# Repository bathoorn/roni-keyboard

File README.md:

# roni-keyboard
kicad roni keyboard project

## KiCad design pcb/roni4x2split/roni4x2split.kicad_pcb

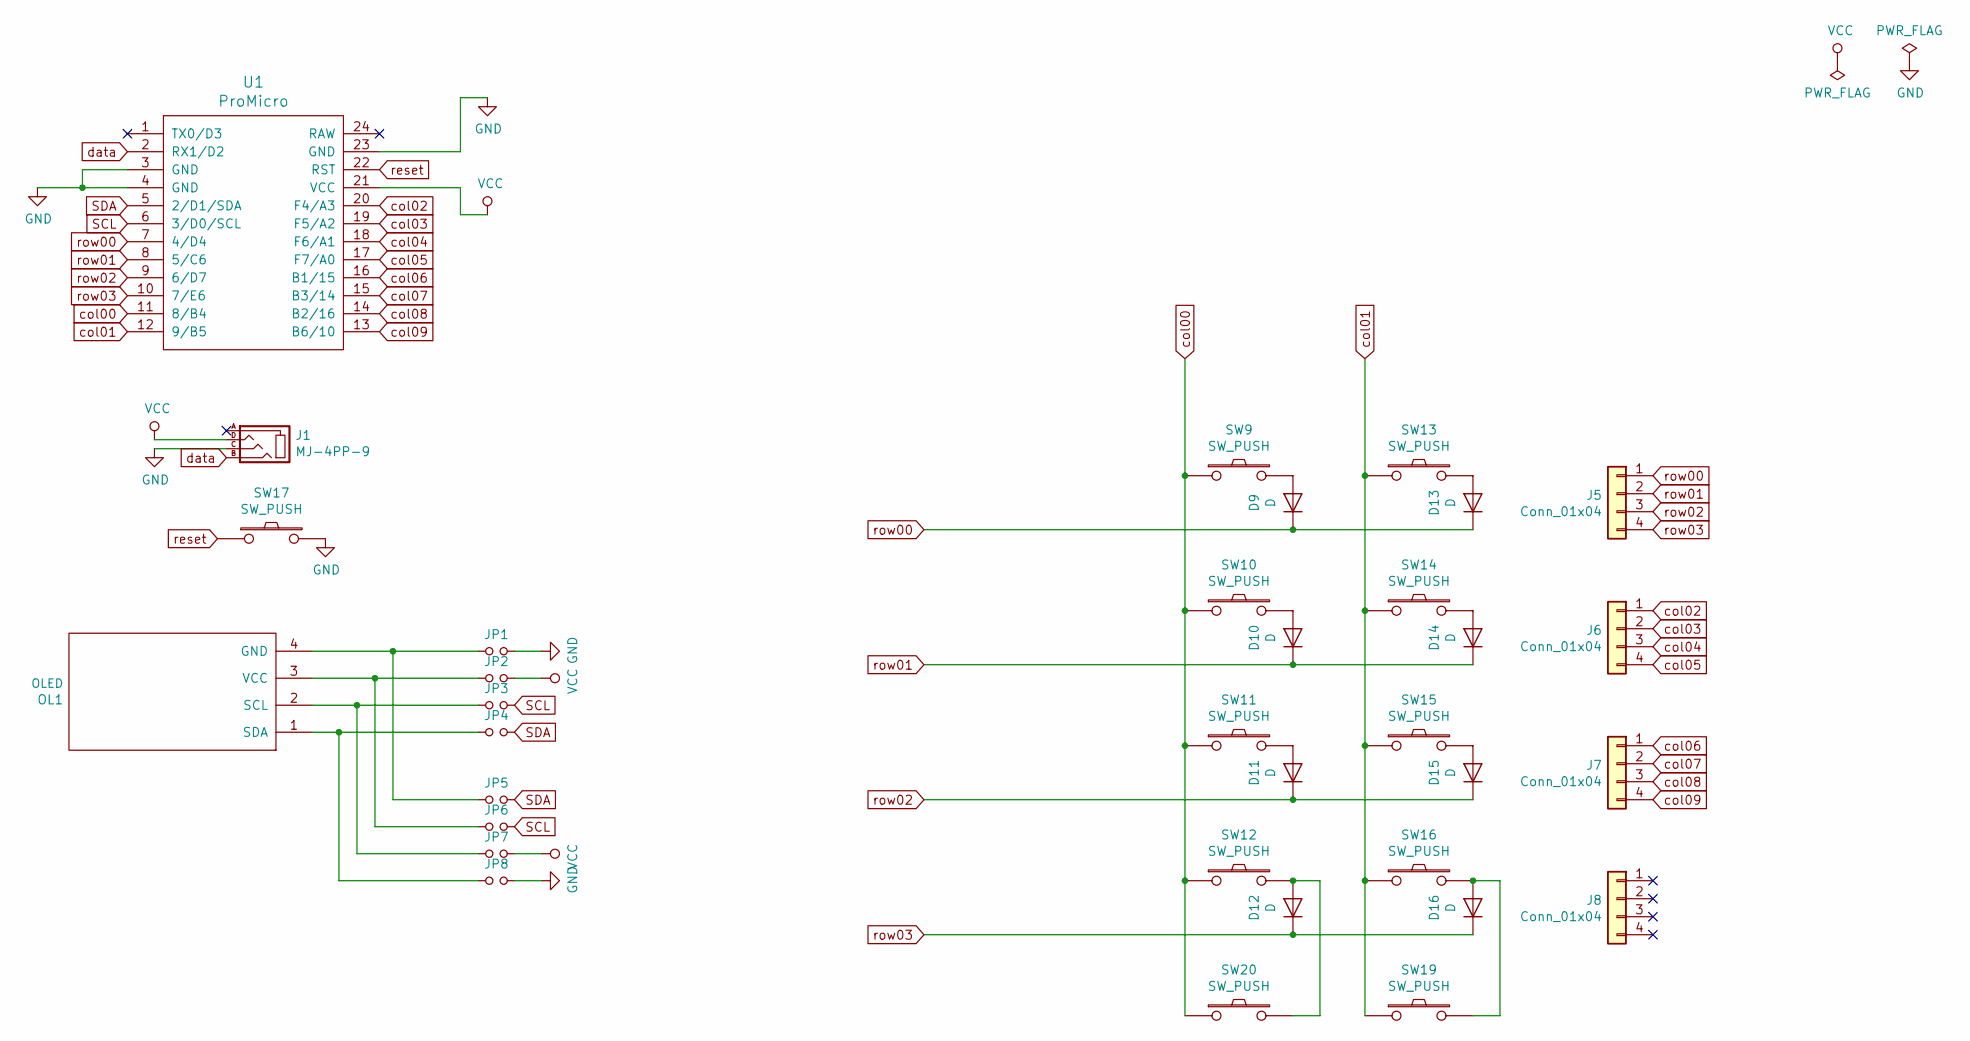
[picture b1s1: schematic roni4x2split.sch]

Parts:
D9, D10, D11, D12, D13, D14, D15, D16: D; D3_TH_SMD
J1: MJ-4PP-9
J5, J6, J7, J8: Conn_01x04; J_1x04_P2.00mm_Vertical
JP1, JP2, JP3, JP4, JP5, JP6, JP7, JP8: Jumper_NO_Small; Jumper
OL1: OLED
SW9, SW10, SW11, SW12, SW13, SW14, SW15, SW16, SW19, SW20: SW_PUSH; SW_MX_reversible
SW17: SW_PUSH; ResetSW
U1: ProMicro; ProMicro_v2

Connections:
GND: J1.C, JP1.2, JP8.2, SW17.2, U1.3 (GND), U1.4 (GND), U1.23 (GND)
unnamed: D9.2 (A), SW9.2
unnamed: D10.2 (A), SW10.2
unnamed: D11.2 (A), SW11.2
unnamed: D12.2 (A), SW12.2, SW20.2
unnamed: D13.2 (A), SW13.2
unnamed: D14.2 (A), SW14.2
unnamed: D15.2 (A), SW15.2
unnamed: D16.2 (A), SW16.2, SW19.2
unnamed: JP1.1, JP5.1, OL1.4 (GND)
unnamed: JP2.1, JP6.1, OL1.3 (VCC)
unnamed: JP3.1, JP7.1, OL1.2 (SCL)
unnamed: JP4.1, JP8.1, OL1.1 (SDA)
SCL: JP3.2, JP6.2, U1.6 (3/D0/SCL)
SDA: JP4.2, JP5.2, U1.5 (2/D1/SDA)
VCC: J1.D, JP2.2, JP7.2, U1.21 (VCC)
col00: SW9.1, SW10.1, SW11.1, SW12.1, SW20.1, U1.11 (8/B4)
col01: SW13.1, SW14.1, SW15.1, SW16.1, SW19.1, U1.12 (9/B5)
col02: J6.1, U1.20 (F4/A3)
col03: J6.2, U1.19 (F5/A2)
col04: J6.3, U1.18 (F6/A1)
col05: J6.4, U1.17 (F7/A0)
col06: J7.1, U1.16 (B1/15)
col07: J7.2, U1.15 (B3/14)
col08: J7.3, U1.14 (B2/16)
col09: J7.4, U1.13 (B6/10)
data: J1.B, U1.2 (RX1/D2)
reset: SW17.1, U1.22 (RST)
row00: D9.1 (K), D13.1 (K), J5.1, U1.7 (4/D4)
row01: D10.1 (K), D14.1 (K), J5.2, U1.8 (5/C6)
row02: D11.1 (K), D15.1 (K), J5.3, U1.9 (6/D7)
row03: D12.1 (K), D16.1 (K), J5.4, U1.10 (7/E6)

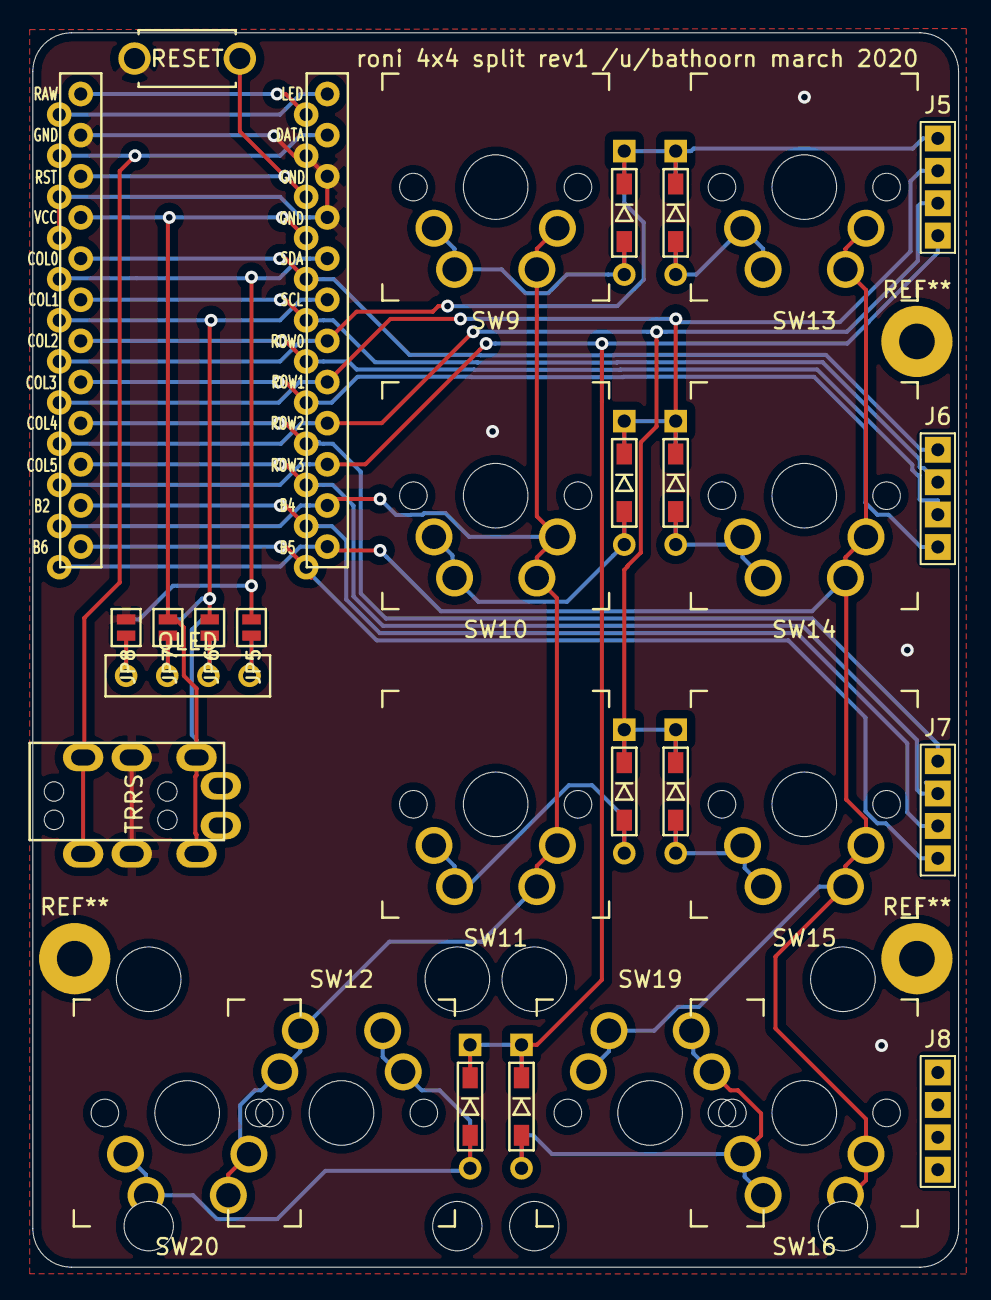
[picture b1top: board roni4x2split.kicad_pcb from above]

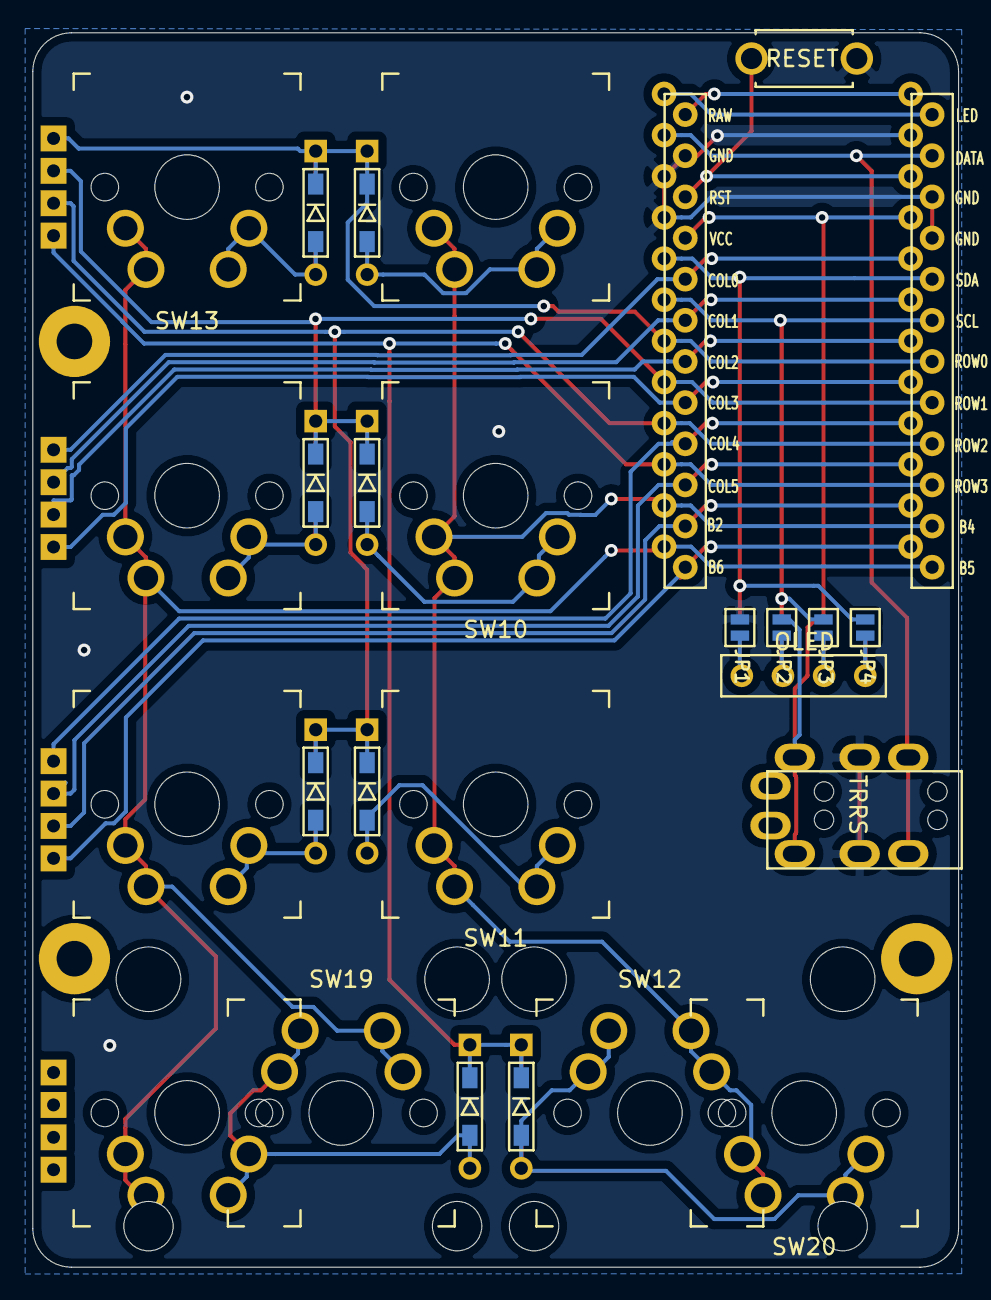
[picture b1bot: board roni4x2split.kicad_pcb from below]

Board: 2 copper layers, 57.1 x 76.2 mm, 34 parts (4 on the bottom side), 32 nets.

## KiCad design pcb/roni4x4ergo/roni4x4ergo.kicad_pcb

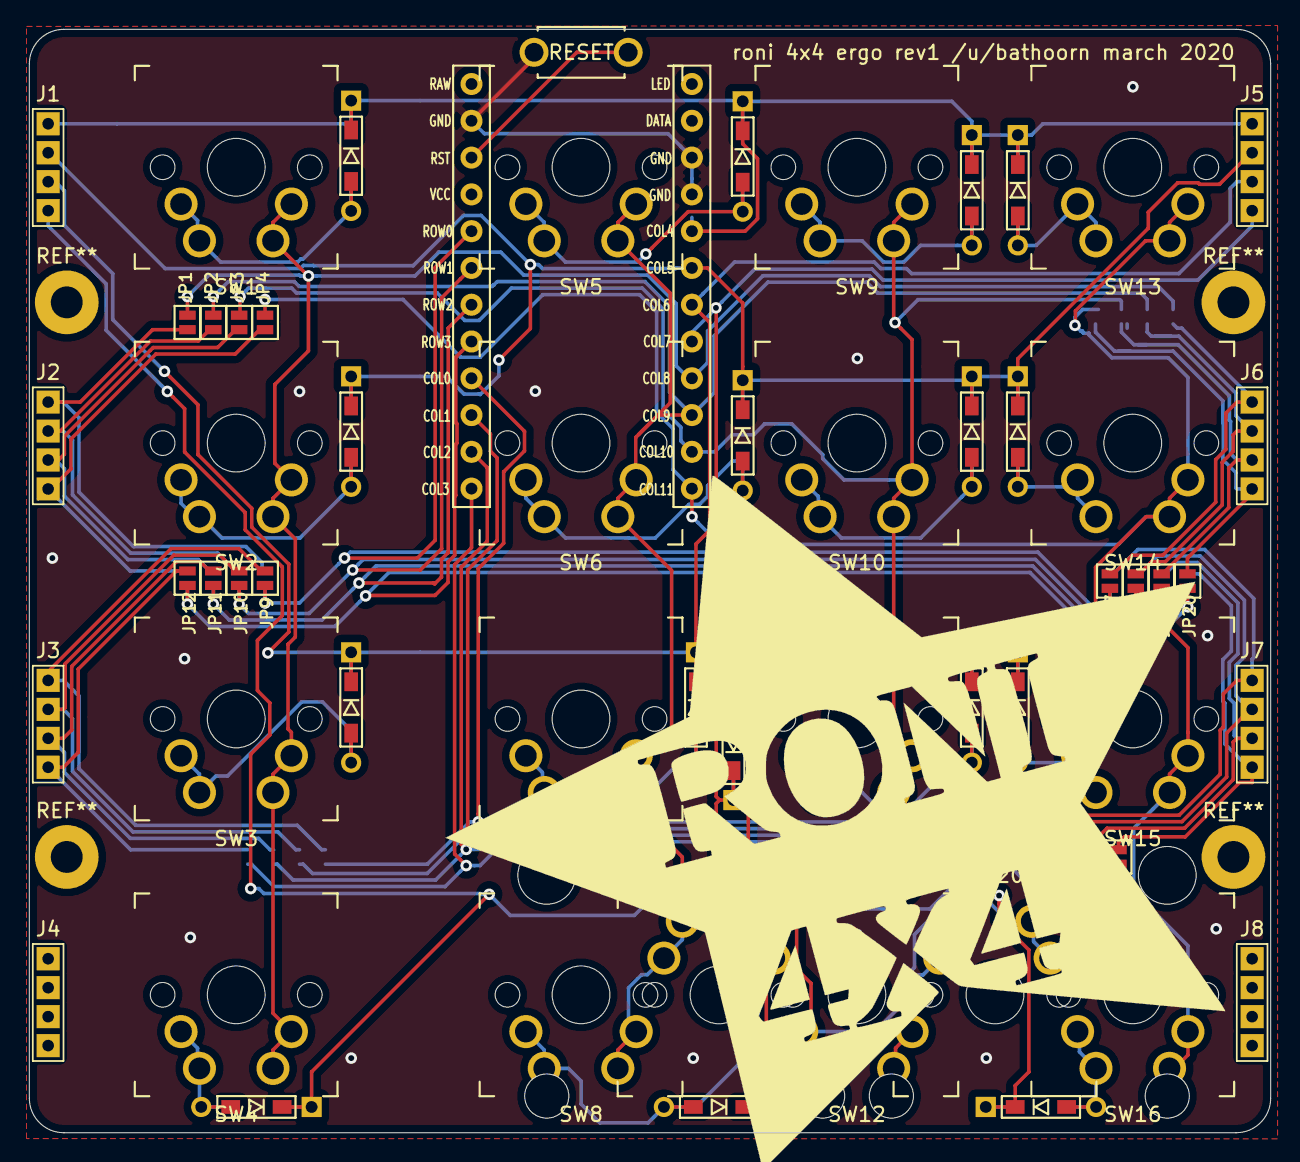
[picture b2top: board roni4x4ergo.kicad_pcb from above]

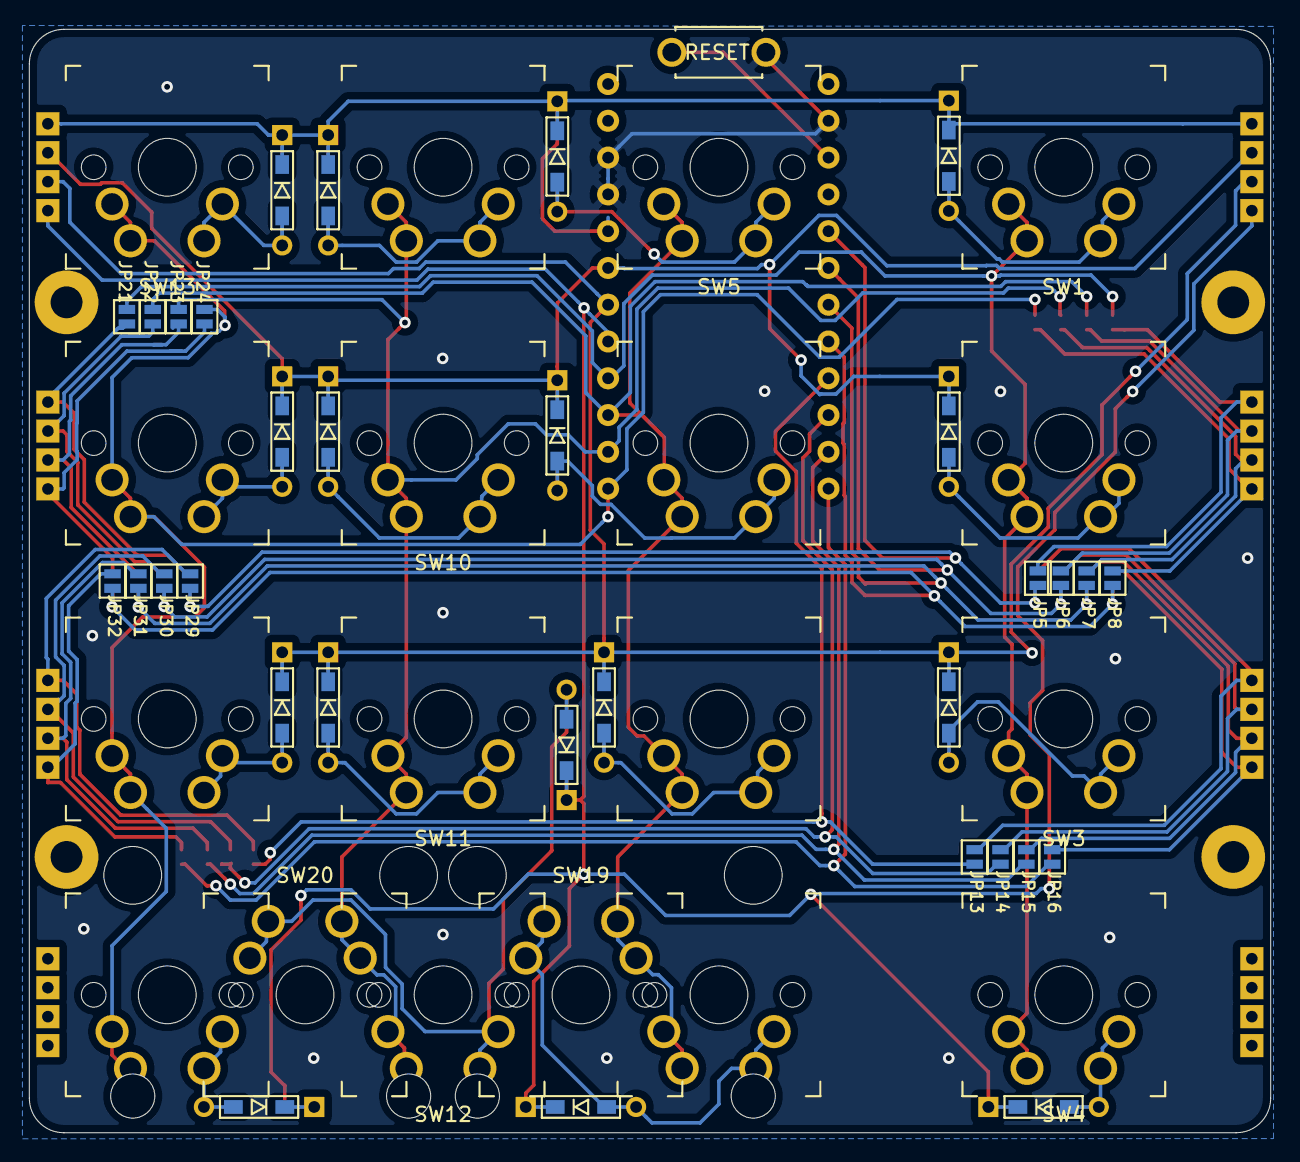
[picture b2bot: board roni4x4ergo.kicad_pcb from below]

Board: 2 copper layers, 85.7 x 76.2 mm, 76 parts (16 on the bottom side), 50 nets.

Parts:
D1, D2, D3, D4, D5, D6, D7, D8, D9, D10, D11, D12, D13, D14, D15, D16: D; D3_TH_SMD
J1, J2, J3, J4, J5, J6, J7, J8: Conn_01x04; J_1x04_P2.00mm_Vertical
JP1, JP2, JP3, JP4, JP5, JP6, JP7, JP8, JP9, JP10, JP11, JP12, JP13, JP14, JP15, JP16, JP17, JP18, JP19, JP20, JP21, JP22, JP23, JP24, JP25, JP26, JP27, JP28, JP29, JP30, JP31, JP32: SolderJumper_2_Open; Jumper
SW1, SW2, SW3, SW4, SW5, SW6, SW7, SW8, SW9, SW10, SW11, SW12, SW13, SW14, SW15, SW16, SW19, SW20: SW_PUSH; SW_MX_reversible
SW17: SW_PUSH; ResetSW
U1: ProMicro; ProMicro_v2_1side

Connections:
GND: SW17.2, U1.3, U1.4, U1.23
unnamed: D1.2, SW1.2
unnamed: D2.2, SW2.2
unnamed: D3.2, SW3.2
unnamed: D4.2, SW4.2
unnamed: D5.2, SW5.2
unnamed: D6.2, SW6.2
unnamed: D7.2, SW7.2
unnamed: D8.2, SW8.2, SW19.2
unnamed: D9.2, SW9.2
unnamed: D10.2, SW10.2
unnamed: D11.2, SW11.2
unnamed: D12.2, SW12.2, SW20.2
unnamed: D13.2, SW13.2
unnamed: D14.2, SW14.2
unnamed: D15.2, SW15.2
unnamed: D16.2, SW16.2
unnamed: J2.1, JP1.2, JP5.2
unnamed: J2.2, JP2.2, JP6.2
unnamed: J2.3, JP3.2, JP7.2
unnamed: J2.4, JP4.2, JP8.2
unnamed: J3.1, JP9.2, JP13.2
unnamed: J3.2, JP10.2, JP14.2
unnamed: J3.3, JP11.2, JP15.2
unnamed: J3.4, JP12.2, JP16.2
unnamed: J6.1, JP17.2, JP21.2
unnamed: J6.2, JP18.2, JP22.2
unnamed: J6.3, JP19.2, JP23.2
unnamed: J6.4, JP20.2, JP24.2
unnamed: J7.1, JP25.2, JP29.2
unnamed: J7.2, JP26.2, JP30.2
unnamed: J7.3, JP27.2, JP31.2
unnamed: J7.4, JP28.2, JP32.2
unnamed: SW17.1, U1.22
col00: JP1.1, JP21.1, SW1.1, SW2.1, SW3.1, SW4.1, U1.9
col01: JP2.1, JP22.1, SW5.1, SW6.1, SW7.1, SW8.1, SW19.1, U1.10
col02: JP3.1, JP23.1, SW9.1, SW10.1, SW11.1, SW12.1, SW20.1, U1.11
col03: JP4.1, JP24.1, SW13.1, SW14.1, SW15.1, SW16.1, U1.12
col04: JP5.1, JP9.1, JP17.1, JP29.1, U1.20
col05: JP6.1, JP10.1, JP18.1, JP30.1, U1.19
col06: JP7.1, JP11.1, JP19.1, JP31.1, U1.18
col07: JP8.1, JP12.1, JP20.1, JP32.1, U1.17
col08: JP13.1, JP25.1, U1.16
col09: JP14.1, JP26.1, U1.15
col10: JP15.1, JP27.1, U1.14
col11: JP16.1, JP28.1, U1.13
row00: D1.1, D5.1, D9.1, D13.1, J1.1, J5.1, U1.5
row01: D2.1, D6.1, D10.1, D14.1, J1.2, J5.2, U1.6
row02: D3.1, D7.1, D11.1, D15.1, J1.3, J5.3, U1.7
row03: D4.1, D8.1, D12.1, D16.1, J1.4, J5.4, U1.8

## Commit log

2020-04-01 add kicad files
